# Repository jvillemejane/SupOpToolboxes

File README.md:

# SupOpToolboxes

**Toolboxes of functions for physicists in photonics**

*Developed by Institut d'Optiqe Graduate School / France*

This project is still **in development**. To contribute, look at the *Collaboration* section.

## Table of Contents
0. [About SupOptique](#about-supoptique)
1. [General Info](#general-info)
2. [Installation](#installation)
3. [How To Use](#how-to-use)
4. [Collaboration](#collaboration)
5. [FAQs](#faqs)

## About SupOptique
Founded in 1917, the Institut d'Optique Graduate School is a world leader in higher education, research and innovation in optics and photonics.

The Institut trains physics engineers, master's students and some of the most innovative PhDs in business and academia.
At the heart of networks of excellence, its international influence is based both on the quality of the training it provides and on its research and technology transfer.

The Institut is a major engineering school member of University Paris-Saclay and is established on the campuses of excellence of Paris-Saclay and Bordeaux, as well as Saint-Etienne.

The scientific contributions of its research center are major : the researchers publish on average one article per week and are quoted 30 times daily.

For more informations : [Institut d'Optique](https://www.institutoptique.fr/en)

## General Info

This repository contains :

- **Python Libraries** for physicists (*python_lib* directory)
- **Python Examples** for physicists (*python_examples* directory)
- **Embedded Librairies** for embedded systems development (Arduino, STM32 MBED, STM32 HAL...)
- **Engineers and Physicits Courses and Problems** (engineers training)

## Installation

You can **clone** this repository into your own work directory (using git) :

```
git clone https://github.com/jvillemejane/SupOpToolboxes.git
```

or

```
git clone git@github.com:jvillemejane/SupOpToolboxes.git
```

If you're not familiar to Git repository, you can also **download** the [archived file - zip](https://github.com/jvillemejane/SupOpToolboxes/archive/refs/heads/main.zip) of the repository.

## How To Use

### Python Libraries

To use **Python Libraries**, you can add the *python_lib* directory to the PYTHONPATH of your Python development interface. 

For example, in **Spyder**, you can select `TOOLS > PYTHONPATH` and add the path to *python_lib* directory.

### Python Examples

## Collaboration

## FAQs

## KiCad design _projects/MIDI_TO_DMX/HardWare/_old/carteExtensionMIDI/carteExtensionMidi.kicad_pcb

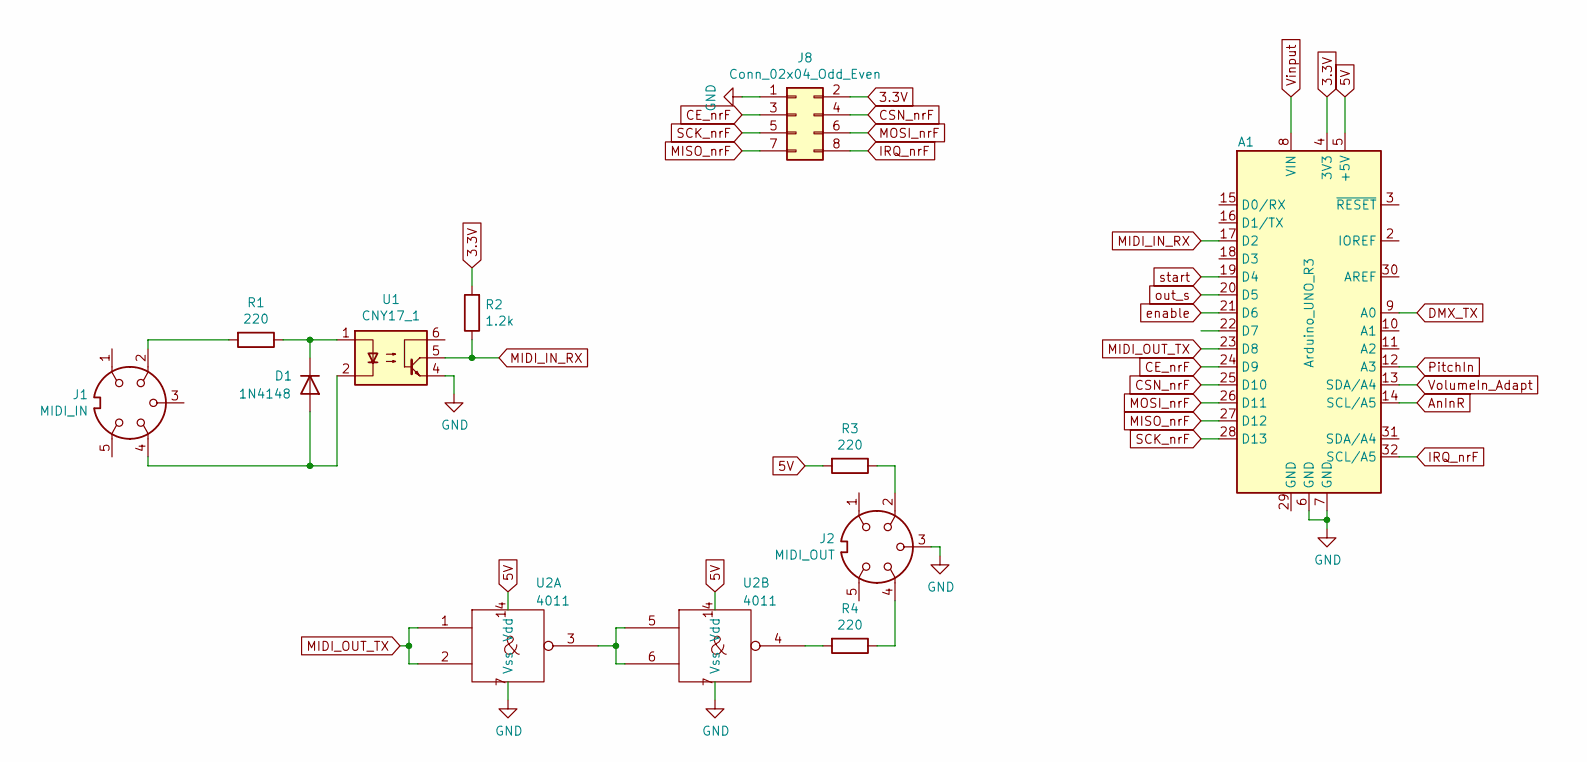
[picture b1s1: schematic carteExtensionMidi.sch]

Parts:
A1: Arduino_UNO_R3
D1: 1N4148; D_DO-35_SOD27_P7.62mm_Horizontal
J1: MIDI_IN; PinHeader_1x05_P2.54mm_Vertical
J2: MIDI_OUT; PinHeader_1x05_P2.54mm_Vertical
J8: Conn_02x04_Odd_Even; PinHeader_2x04_P2.54mm_Vertical
R1, R3, R4: 220; R_Axial_DIN0207_L6.3mm_D2.5mm_P10.16mm_Horizontal
R2: 1.2k; R_Axial_DIN0207_L6.3mm_D2.5mm_P10.16mm_Horizontal
U1: CNY17_1; DIP-6_W7.62mm_LongPads
U2: 4011; DIP-14_W7.62mm_LongPads

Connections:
3.3V: A1.4 (3V3), J8.2, R2.2
5V: A1.5 (+5V), R3.2, U2.14 (Vdd)
AnInR: A1.14 (SCL/A5)
CE_nrF: A1.24 (D9), J8.3
CSN_nrF: A1.25 (D10), J8.4
DMX_TX: A1.9 (A0)
GND: A1.6 (GND), A1.7 (GND), J2.3, J8.1, U1.4, U2.7 (Vss)
IRQ_nrF: A1.32 (SCL/A5), J8.8
MIDI_IN_RX: A1.17 (D2), R2.1, U1.5
MIDI_OUT_TX: A1.23 (D8), U2.1, U2.2
MISO_nrF: A1.27 (D12), J8.7
MOSI_nrF: A1.26 (D11), J8.6
unnamed: D1.1 (K), R1.1, U1.1
unnamed: D1.2 (A), J1.4, U1.2
unnamed: J1.2, R1.2
unnamed: J2.2, R3.1
unnamed: J2.4, R4.1
unnamed: R4.2, U2.4
unnamed: U2.3, U2.5, U2.6
PitchIn: A1.12 (A3)
SCK_nrF: A1.28 (D13), J8.5
Vinput: A1.8 (VIN)
VolumeIn_Adapt: A1.13 (SDA/A4)
enable: A1.21 (D6)
out_s: A1.20 (D5)
start: A1.19 (D4)

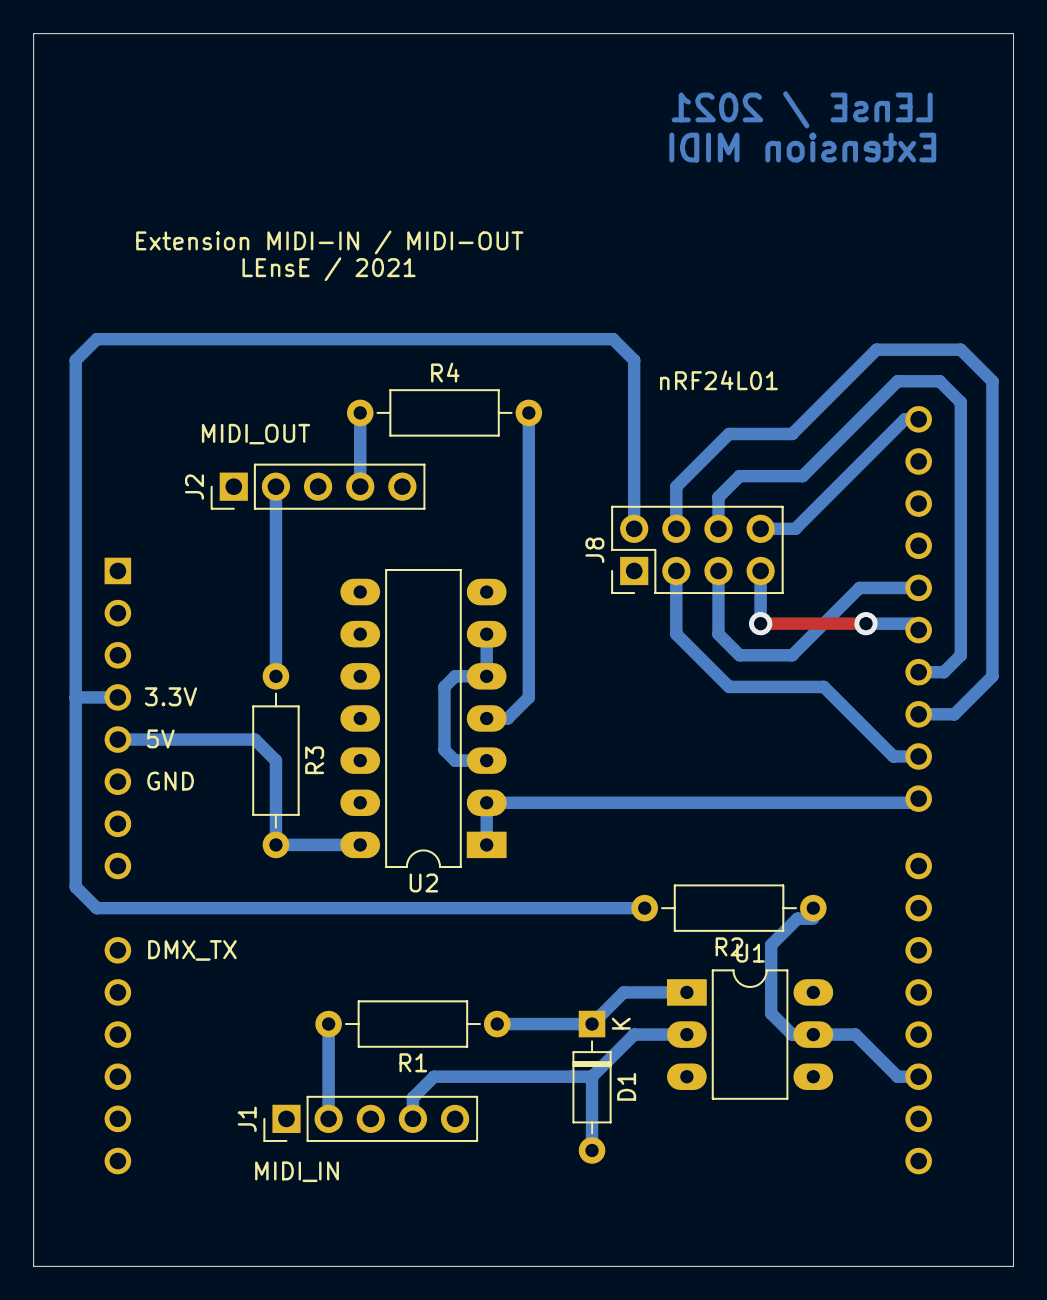
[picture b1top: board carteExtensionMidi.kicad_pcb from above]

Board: 2 copper layers, 59.1 x 74.3 mm, 11 parts (1 on the bottom side), 18 nets.

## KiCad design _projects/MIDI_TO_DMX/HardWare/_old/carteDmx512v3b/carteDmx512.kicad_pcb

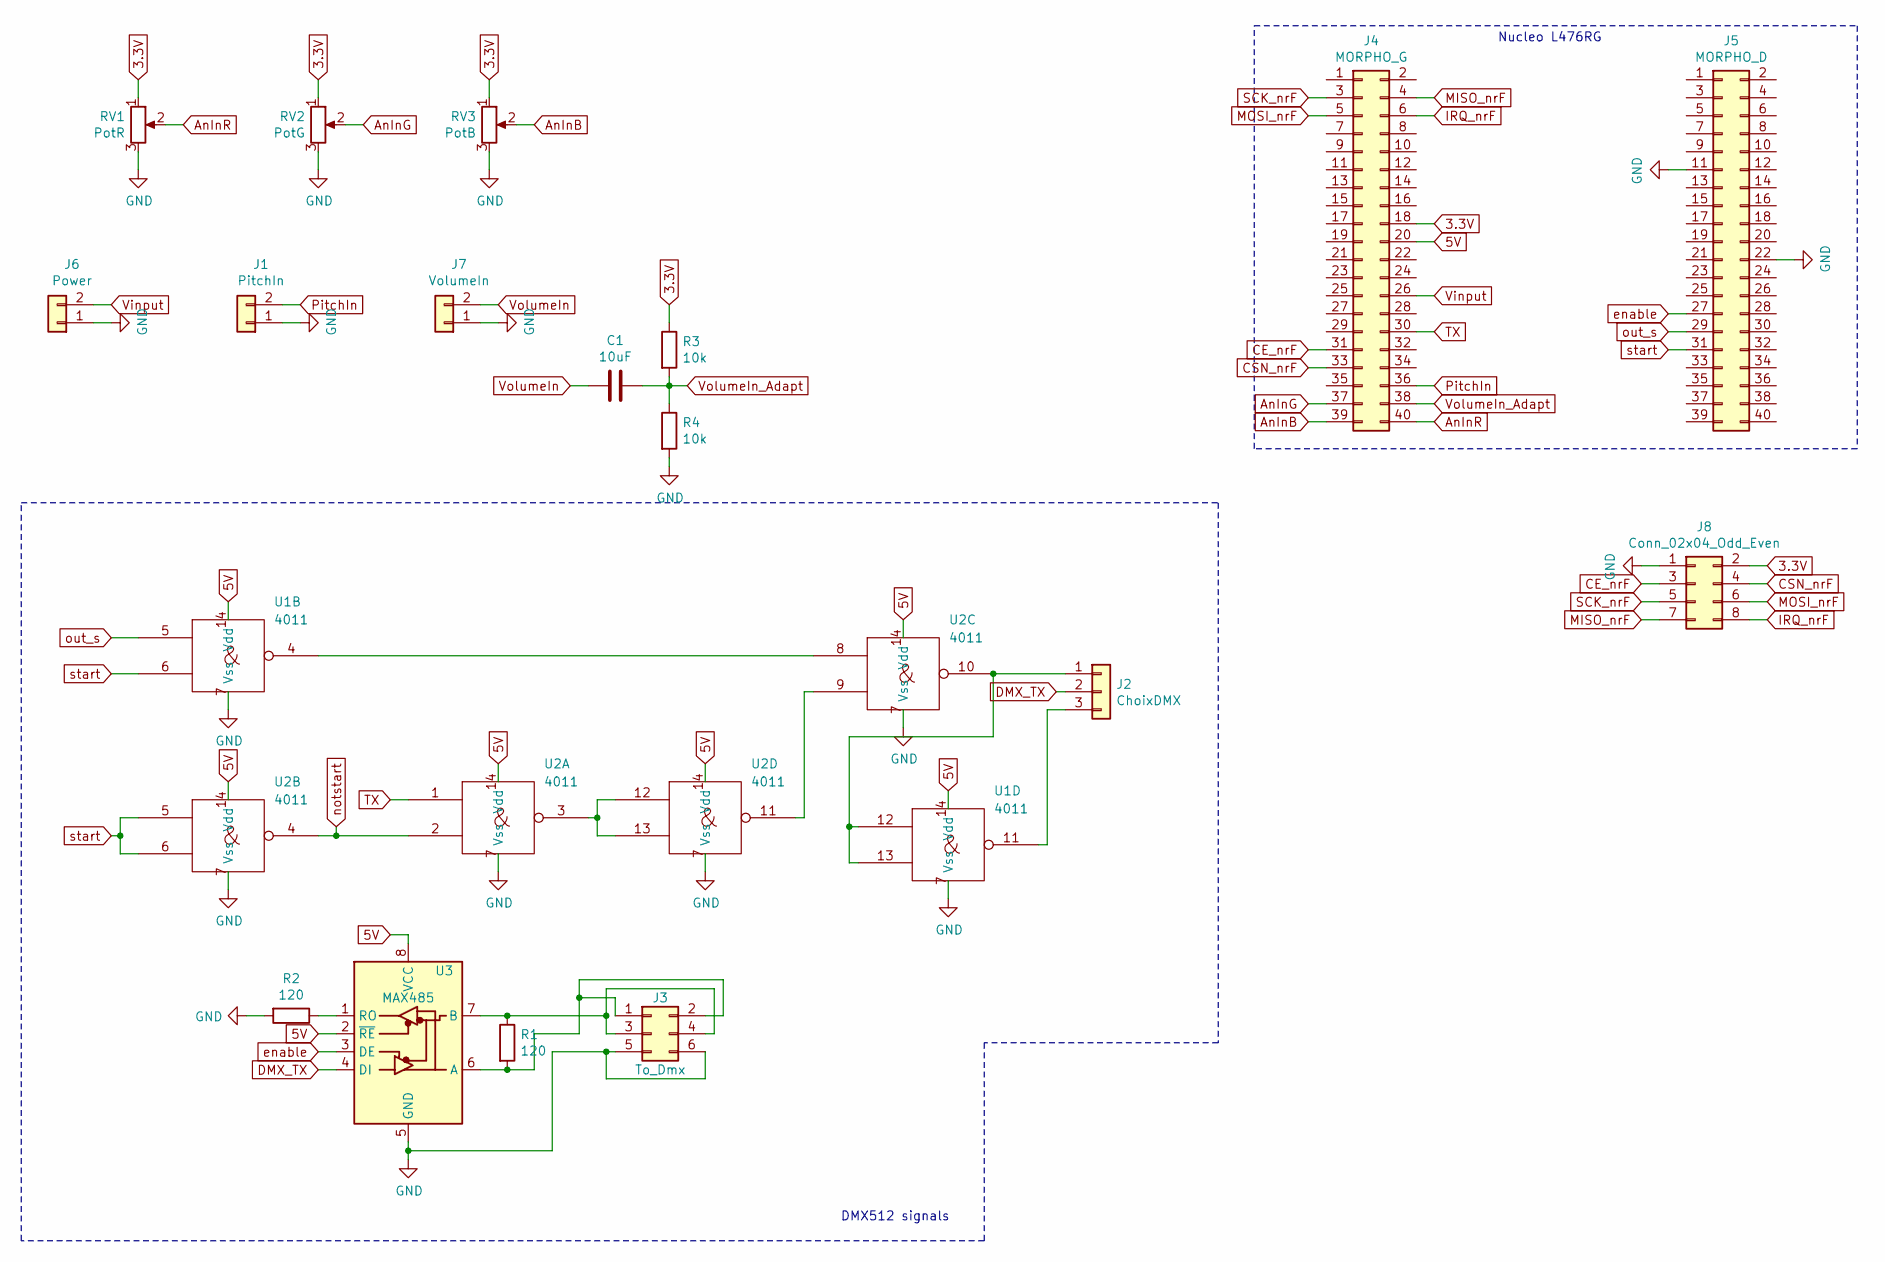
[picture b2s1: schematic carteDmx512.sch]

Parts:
C1: 10uF; CP_Radial_D5.0mm_P2.50mm
J1: PitchIn; TerminalBlock_Phoenix_MKDS-3-2-5.08_1x02_P5.08mm_Horizontal
J2: ChoixDMX; PinHeader_1x03_P2.54mm_Horizontal
J3: To_Dmx; PinHeader_2x03_P2.54mm_Vertical
J4: MORPHO_G; PinHeader_2x20_P2.54mm_Vertical
J5: MORPHO_D; PinHeader_2x20_P2.54mm_Vertical
J6: Power; TerminalBlock_Phoenix_MKDS-3-2-5.08_1x02_P5.08mm_Horizontal
J7: VolumeIn; TerminalBlock_Phoenix_MKDS-3-2-5.08_1x02_P5.08mm_Horizontal
J8: Conn_02x04_Odd_Even; PinHeader_2x04_P2.54mm_Vertical
R1, R2: 120; R_Axial_DIN0207_L6.3mm_D2.5mm_P10.16mm_Horizontal
R3, R4: 10k; R_Axial_DIN0207_L6.3mm_D2.5mm_P10.16mm_Horizontal
RV1: PotR; Potentiometer_Vishay_T73YP_Vertical
RV2: PotG; Potentiometer_Vishay_T73YP_Vertical
RV3: PotB; Potentiometer_Vishay_T73YP_Vertical
U1, U2: 4011; DIP-14_W7.62mm_Socket_LongPads
U3: MAX485; DIP-8_W7.62mm_Socket_LongPads

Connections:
3.3V: J4.18, J8.2, R3.1, RV1.1, RV2.1, RV3.1
5V: J4.20, U1.14 (Vdd), U2.14 (Vdd), U3.2 (~RE), U3.8 (VCC)
AnInB: J4.39, RV3.2
AnInG: J4.37, RV2.2
AnInR: J4.40, RV1.2
CE_nrF: J4.31, J8.3
CSN_nrF: J4.33, J8.4
DMX_TX: J2.2, U3.4 (DI)
GND: J1.1, J3.5, J3.6, J5.11, J5.22, J6.1, J7.1, J8.1, R2.2, R4.2, RV1.3, RV2.3, RV3.3, U1.7 (Vss), U2.7 (Vss), U3.5 (GND)
IRQ_nrF: J4.6, J8.8
MISO_nrF: J4.4, J8.7
MOSI_nrF: J4.5, J8.6
unnamed: J2.1, U1.12, U1.13, U2.10
unnamed: J2.3, U1.11
unnamed: J3.1, J3.2, R1.2, U3.6 (A)
unnamed: J3.3, J3.4, R1.1, U3.7 (B)
unnamed: R2.1, U3.1 (RO)
unnamed: U1.4, U2.8
unnamed: U2.9, U2.11
unnamed: U2.3, U2.12, U2.13
PitchIn: J1.2, J4.36
SCK_nrF: J4.3, J8.5
TX: J4.30, U2.1
Vinput: J4.26, J6.2
VolumeIn: C1.2, J7.2
VolumeIn_Adapt: C1.1, J4.38, R3.2, R4.1
enable: J5.27, U3.3 (DE)
notstart: U2.2, U2.4
out_s: J5.29, U1.5
start: J5.31, U1.6, U2.5, U2.6

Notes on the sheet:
Nucleo L476RG
DMX512 signals

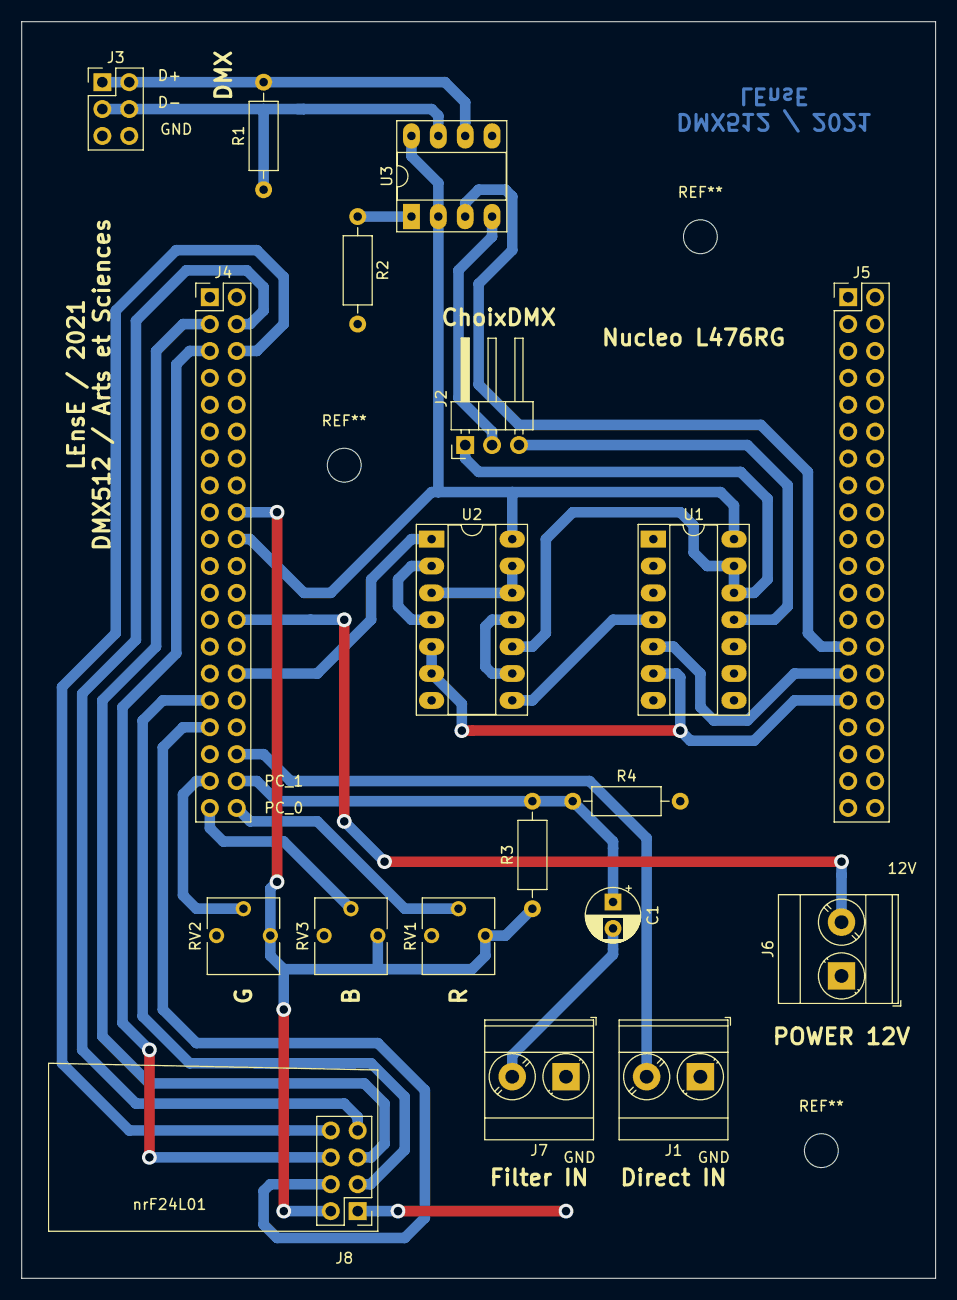
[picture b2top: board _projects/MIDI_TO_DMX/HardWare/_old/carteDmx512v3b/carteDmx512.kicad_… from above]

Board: 2 copper layers, 86.4 x 118.7 mm, 19 parts (0 on the bottom side), 30 nets.

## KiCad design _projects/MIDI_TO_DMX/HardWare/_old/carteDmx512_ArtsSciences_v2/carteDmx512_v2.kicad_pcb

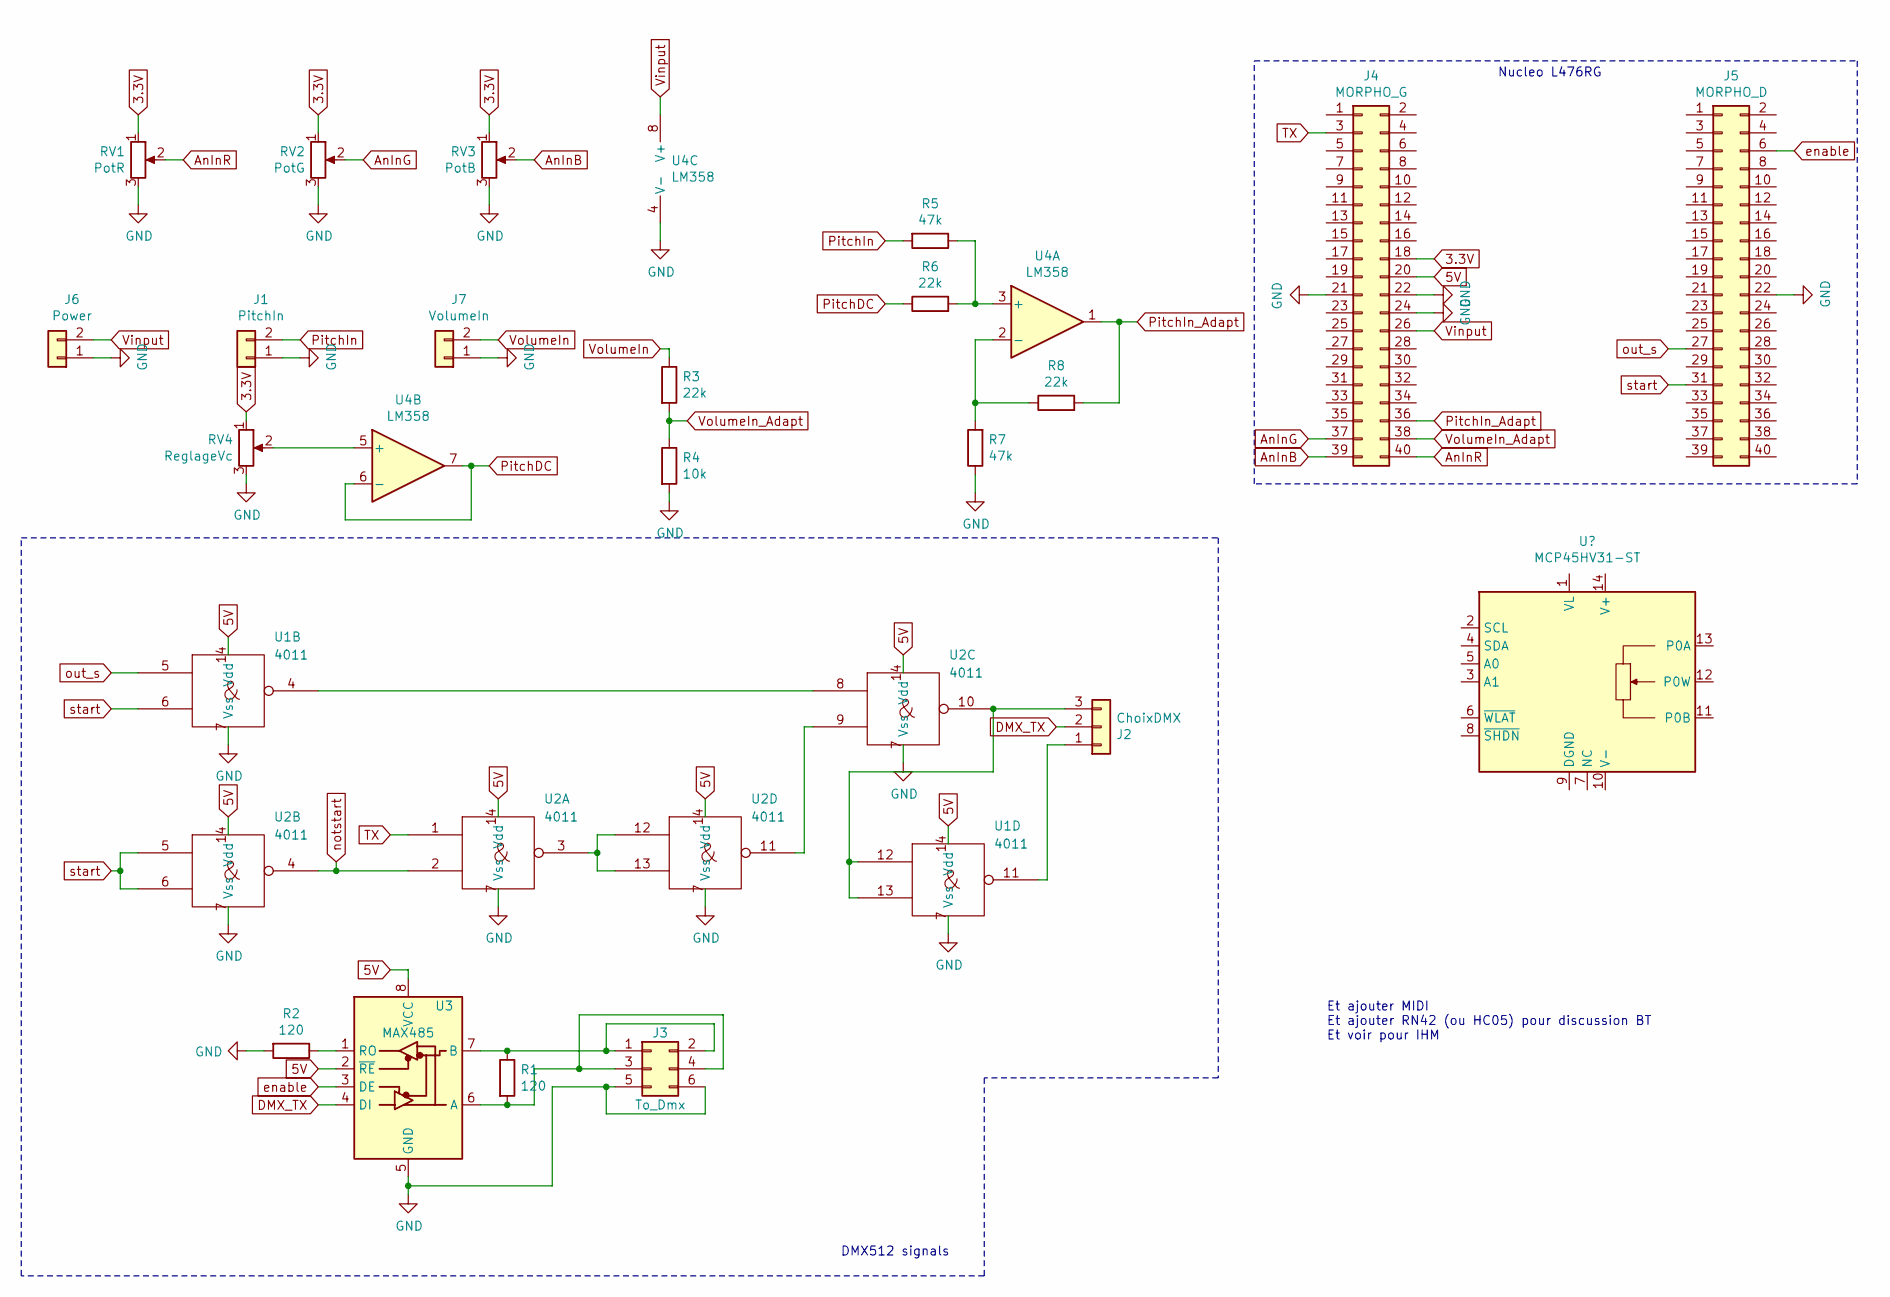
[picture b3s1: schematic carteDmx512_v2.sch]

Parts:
J1: PitchIn; TerminalBlock_Phoenix_MKDS-3-2-5.08_1x02_P5.08mm_Horizontal
J2: ChoixDMX; PinHeader_1x03_P2.54mm_Horizontal
J3: To_Dmx; PinHeader_2x03_P2.54mm_Vertical
J4: MORPHO_G; PinHeader_2x20_P2.54mm_Vertical
J5: MORPHO_D; PinHeader_2x20_P2.54mm_Vertical
J6: Power; TerminalBlock_Phoenix_MKDS-3-2-5.08_1x02_P5.08mm_Horizontal
J7: VolumeIn; TerminalBlock_Phoenix_MKDS-3-2-5.08_1x02_P5.08mm_Horizontal
R1, R2: 120; R_Axial_DIN0207_L6.3mm_D2.5mm_P10.16mm_Horizontal
R3, R6, R8: 22k; R_Axial_DIN0207_L6.3mm_D2.5mm_P10.16mm_Horizontal
R4: 10k; R_Axial_DIN0207_L6.3mm_D2.5mm_P10.16mm_Horizontal
R5, R7: 47k; R_Axial_DIN0207_L6.3mm_D2.5mm_P10.16mm_Horizontal
RV1: PotR; Potentiometer_Vishay_T73YP_Vertical
RV2: PotG; Potentiometer_Vishay_T73YP_Vertical
RV3: PotB; Potentiometer_Vishay_T73YP_Vertical
RV4: ReglageVc; Potentiometer_Vishay_T73YP_Vertical
U1, U2: 4011; DIP-14_W7.62mm_Socket_LongPads
U3: MAX485; DIP-8_W7.62mm_Socket_LongPads
U4: LM358; DIP-8_W7.62mm_Socket_LongPads

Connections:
3.3V: J4.18, RV1.1, RV2.1, RV3.1, RV4.1
5V: J4.20, U1.14 (Vdd), U2.14 (Vdd), U3.2 (~RE), U3.8 (VCC)
AnInB: J4.39, RV3.2
AnInG: J4.37, RV2.2
AnInR: J4.40, RV1.2
DMX_TX: J2.2, U3.4 (DI)
GND: J1.1, J3.5, J3.6, J4.21, J4.22, J4.24, J5.22, J6.1, J7.1, R2.2, R4.2, R7.1, RV1.3, RV2.3, RV3.3, RV4.3, U1.7 (Vss), U2.7 (Vss), U3.5 (GND), U4.4 (V-)
unnamed: J2.1, U1.11
unnamed: J2.3, U1.12, U1.13, U2.10
unnamed: J3.1, J3.2, R1.1, U3.7 (B)
unnamed: J3.3, J3.4, R1.2, U3.6 (A)
unnamed: R2.1, U3.1 (RO)
unnamed: R5.1, R6.2, U4.3 (+)
unnamed: R7.2, R8.1, U4.2 (-)
unnamed: RV4.2, U4.5 (+)
unnamed: U1.4, U2.8
unnamed: U2.9, U2.11
unnamed: U2.3, U2.12, U2.13
PitchDC: R6.1, U4.6 (-), U4.7
PitchIn: J1.2, R5.2
PitchIn_Adapt: J4.36, R8.2, U4.1
TX: J4.3, U2.1
Vinput: J4.26, J6.2, U4.8 (V+)
VolumeIn: J7.2, R3.1
VolumeIn_Adapt: J4.38, R3.2, R4.1
enable: J5.6, U3.3 (DE)
notstart: U2.2, U2.4
out_s: J5.27, U1.5
start: J5.31, U1.6, U2.5, U2.6

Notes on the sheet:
Nucleo L476RG
DMX512 signals
Et ajouter MIDI Et ajouter RN42 (ou HC05) pour discussion BT Et voir pour IHM

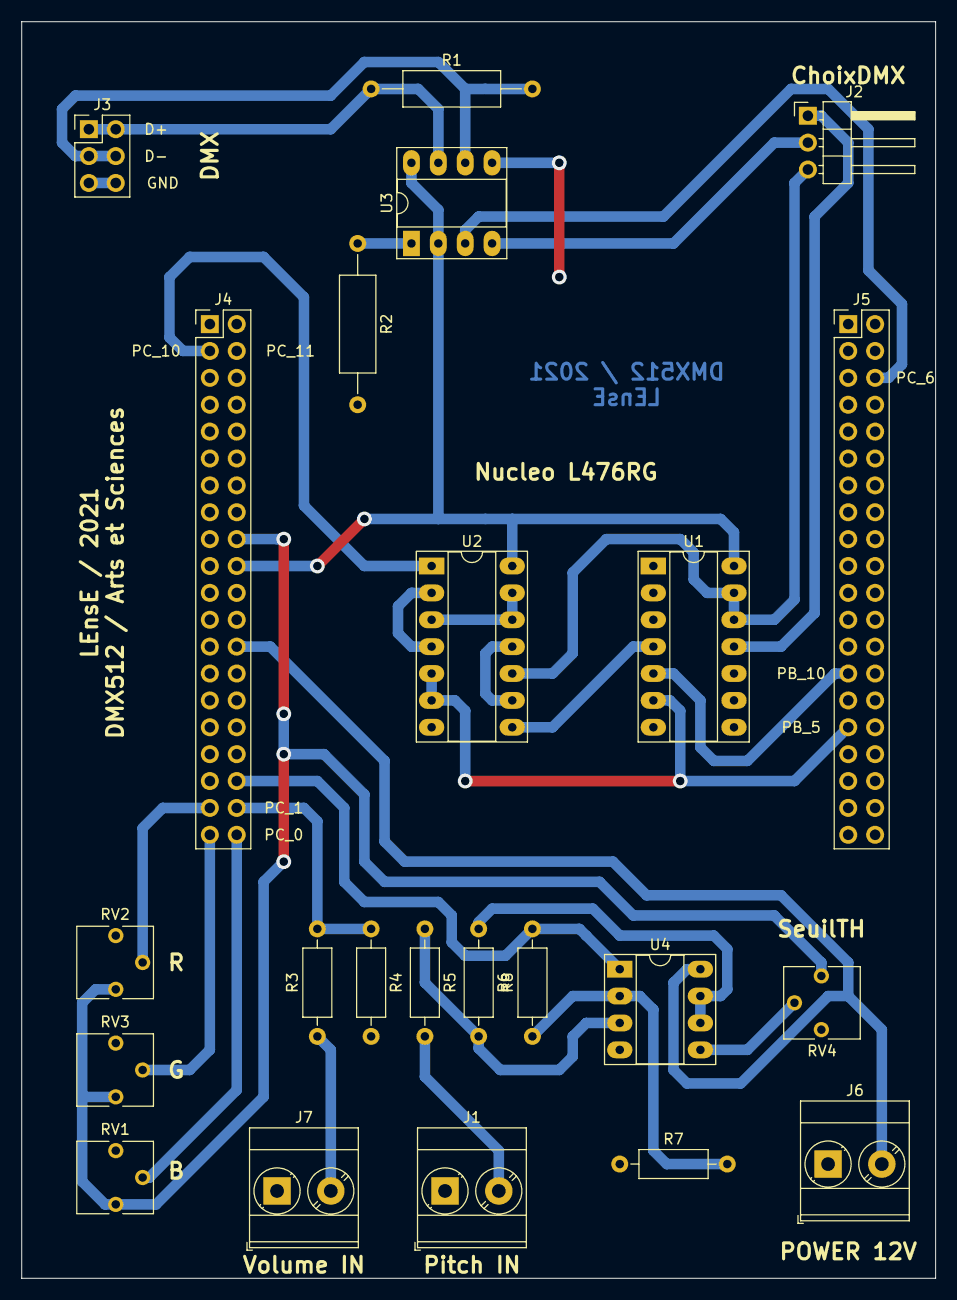
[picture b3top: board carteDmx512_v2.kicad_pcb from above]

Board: 2 copper layers, 86.4 x 118.7 mm, 23 parts (0 on the bottom side), 29 nets.

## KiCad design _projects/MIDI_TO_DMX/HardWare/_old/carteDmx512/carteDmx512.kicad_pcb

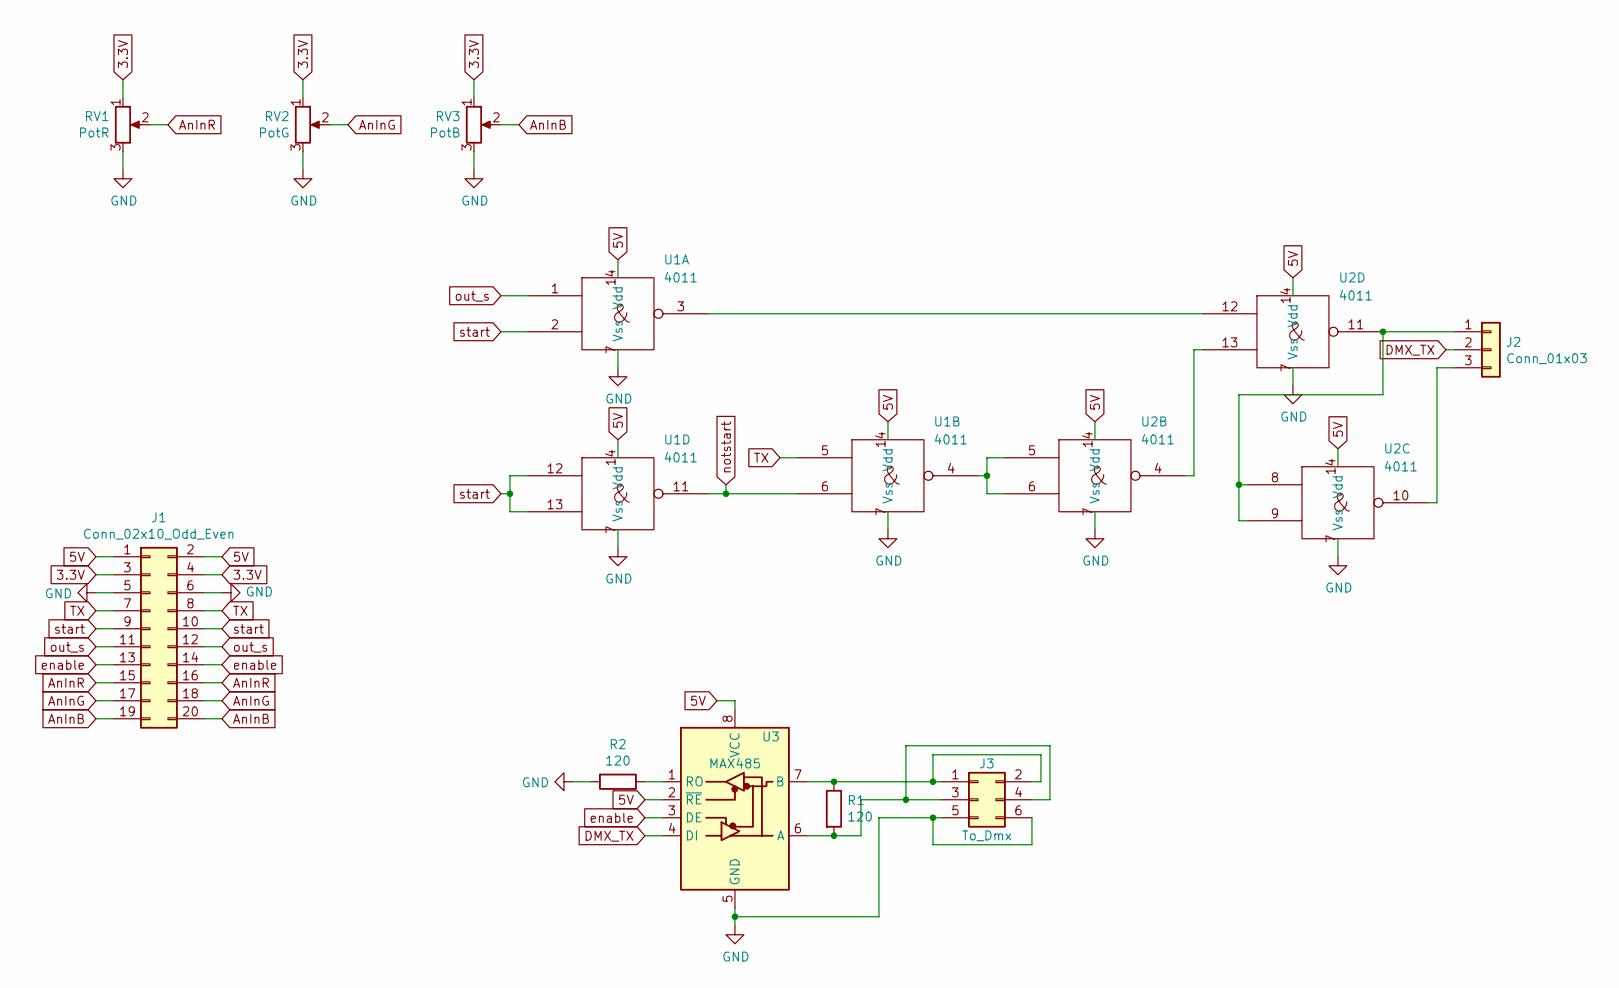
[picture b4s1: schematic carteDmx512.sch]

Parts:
J1: Conn_02x10_Odd_Even; PinHeader_2x10_P2.54mm_Vertical
J2: Conn_01x03; PinHeader_1x03_P2.54mm_Vertical
J3: To_Dmx; PinHeader_2x03_P2.54mm_Vertical
R1, R2: 120; R_Axial_DIN0309_L9.0mm_D3.2mm_P15.24mm_Horizontal
RV1: PotR; Potentiometer_Vishay_T73YP_Vertical
RV2: PotG; Potentiometer_Vishay_T73YP_Vertical
RV3: PotB; Potentiometer_Vishay_T73YP_Vertical
U1, U2: 4011; DIP-14_W7.62mm_Socket_LongPads
U3: MAX485; DIP-8_W7.62mm_Socket_LongPads

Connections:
3.3V: J1.3, J1.4, RV1.1, RV2.1, RV3.1
5V: J1.1, J1.2, U1.14 (Vdd), U2.14 (Vdd), U3.2 (~RE), U3.8 (VCC)
AnInB: J1.19, J1.20, RV3.2
AnInG: J1.17, J1.18, RV2.2
AnInR: J1.15, J1.16, RV1.2
DMX_TX: J2.2, U3.4 (DI)
GND: J1.5, J1.6, J3.5, J3.6, R2.2, RV1.3, RV2.3, RV3.3, U1.7 (Vss), U2.7 (Vss), U3.5 (GND)
unnamed: J2.1, U2.8, U2.9, U2.11
unnamed: J2.3, U2.10
unnamed: J3.1, J3.2, R1.1, U3.7 (B)
unnamed: J3.3, J3.4, R1.2, U3.6 (A)
unnamed: R2.1, U3.1 (RO)
unnamed: U1.3, U2.12
unnamed: U1.4, U2.5, U2.6
unnamed: U2.4, U2.13
TX: J1.7, J1.8, U1.5
enable: J1.13, J1.14, U3.3 (DE)
notstart: U1.6, U1.11
out_s: J1.11, J1.12, U1.1
start: J1.9, J1.10, U1.2, U1.12, U1.13

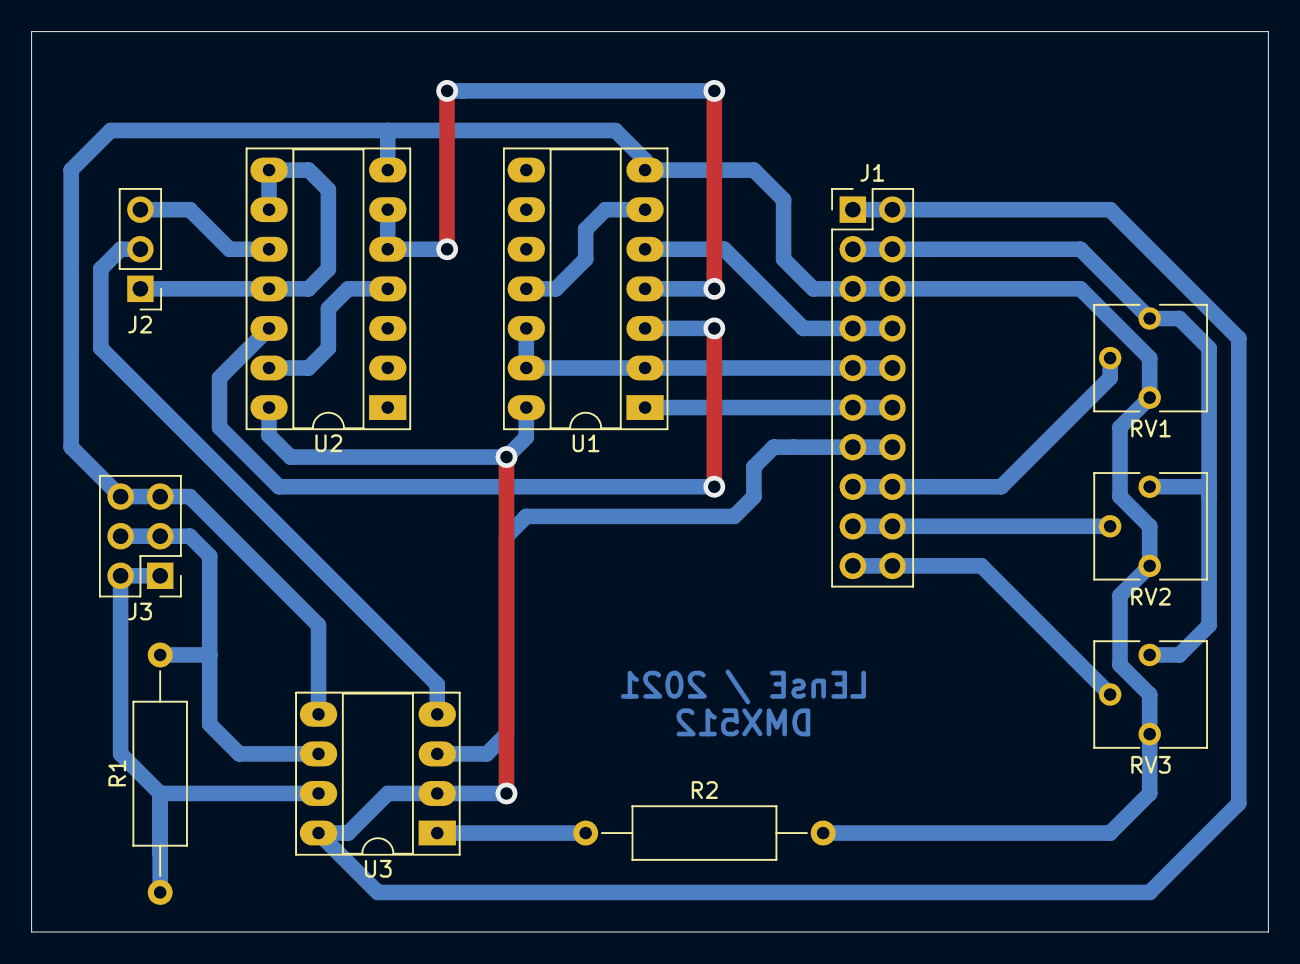
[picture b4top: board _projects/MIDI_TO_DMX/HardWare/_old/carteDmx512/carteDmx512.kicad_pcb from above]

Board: 2 copper layers, 79.4 x 57.8 mm, 11 parts (0 on the bottom side), 20 nets.

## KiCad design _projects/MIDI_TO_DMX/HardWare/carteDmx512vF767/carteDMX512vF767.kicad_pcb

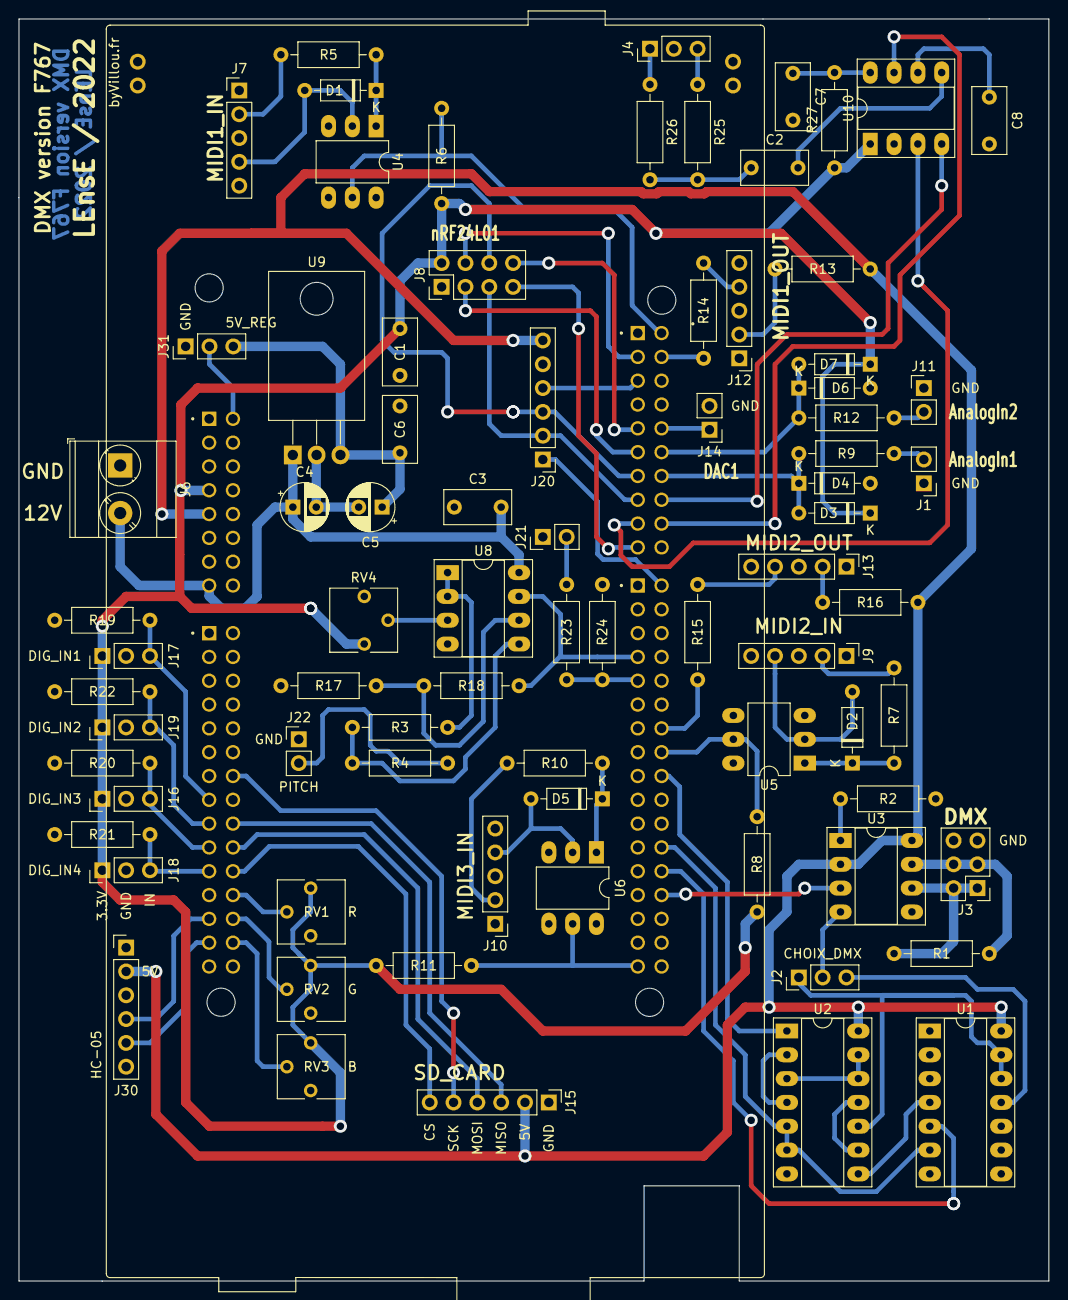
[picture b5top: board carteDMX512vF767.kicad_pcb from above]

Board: 2 copper layers, 109.9 x 134.6 mm, 79 parts (0 on the bottom side), 81 nets.

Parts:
C1, C3, C6, C8: 100nF; C_Rect_L7.0mm_W3.5mm_P5.00mm
C2: 10nF; C_Rect_L7.0mm_W3.5mm_P5.00mm
C4, C5: 100uF; CP_Radial_D5.0mm_P2.50mm
C7: 33pF; C_Rect_L7.0mm_W3.5mm_P5.00mm
D1, D2, D3, D4, D5, D6, D7: 1N4148; D_DO-35_SOD27_P7.62mm_Horizontal
J1: DirectIn; PinHeader_1x02_P2.54mm_Vertical
J2: ChoixDMX; PinHeader_1x03_P2.54mm_Vertical
J3: To_Dmx; PinHeader_2x03_P2.54mm_Vertical
J4: JackInStereo; PinHeader_1x03_P2.54mm_Vertical
J6: Power; TerminalBlock_Phoenix_MKDS-3-2-5.08_1x02_P5.08mm_Horizontal
J7: MIDI1_IN; PinHeader_1x05_P2.54mm_Vertical
J8: nRF24L01; PinHeader_2x04_P2.54mm_Vertical
J9: MIDI2_IN; PinHeader_1x05_P2.54mm_Vertical
J10: MIDI3_IN; PinHeader_1x05_P2.54mm_Vertical
J11: FilterIn; PinHeader_1x02_P2.54mm_Vertical
J12: MIDI1_OUT; PinHeader_1x05_P2.54mm_Vertical
J13: MIDI2_OUT; PinHeader_1x05_P2.54mm_Vertical
J14: Test_D13; PinHeader_1x02_P2.54mm_Vertical
J15: SD_Card; PinHeader_1x06_P2.54mm_Vertical
J16: DigIn3; PinHeader_1x03_P2.54mm_Vertical
J17: DigIn1; PinHeader_1x03_P2.54mm_Vertical
J18: DigIn4; PinHeader_1x03_P2.54mm_Vertical
J19: DigIn2; PinHeader_1x03_P2.54mm_Vertical
J20: LCD_Out; PinHeader_1x06_P2.54mm_Vertical
J21: Volume_In_In; PinHeader_1x02_P2.54mm_Vertical
J22: Pitch_In_In; PinHeader_1x02_P2.54mm_Vertical
J30: BT_HC05; PinHeader_1x06_P2.54mm_Vertical
J31: BandeauLED; PinHeader_1x03_P2.54mm_Vertical
R1, R2: 120; R_Axial_DIN0207_L6.3mm_D2.5mm_P10.16mm_Horizontal
R3, R18, R23, R25, R26: 22k; R_Axial_DIN0207_L6.3mm_D2.5mm_P10.16mm_Horizontal
R4, R17: 47k; R_Axial_DIN0207_L6.3mm_D2.5mm_P10.16mm_Horizontal
R5, R7, R10, R13, R14, R15, R16: 220; R_Axial_DIN0207_L6.3mm_D2.5mm_P10.16mm_Horizontal
R6, R8, R9, R11, R12: 1.2k; R_Axial_DIN0207_L6.3mm_D2.5mm_P10.16mm_Horizontal
R19, R20, R21, R22, R24: 10k; R_Axial_DIN0207_L6.3mm_D2.5mm_P10.16mm_Horizontal
R27: 220k; R_Axial_DIN0207_L6.3mm_D2.5mm_P10.16mm_Horizontal
RV1: PotR; Potentiometer_Vishay_T73YP_Vertical
RV2: PotG; Potentiometer_Vishay_T73YP_Vertical
RV3: PotB; Potentiometer_Vishay_T73YP_Vertical
RV4: 22k; Potentiometer_Vishay_T73YP_Vertical
U1, U2: 4011; DIP-14_W7.62mm_Socket_LongPads
U3: MAX485; DIP-8_W7.62mm_Socket_LongPads
U4, U5, U6: CNY17-1; DIP-6_W7.62mm_LongPads
U7: NUCLEO144-H7A3ZI-Q; ST_Zio_Connectors_144_STLink
U8: LM358; DIP-8_W7.62mm_Socket_LongPads
U9: L7805; TO-220-3_Horizontal_TabDown
U10: MSGEQ7; DIP-8_W7.62mm_Socket_LongPads

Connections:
3.3V: C1.2, D3.1, D6.1, J8.2, J16.1, J17.1, J18.1, J19.1, R6.2, R8.2, R11.2, R27.1, RV1.1, RV2.1, RV3.1, RV4.1, U7.CN8_7, U10.1
5V: J15.2, J20.6, J30.2, R13.2, R16.2, U1.14, U2.14, U3.2, U3.8, U7.CN8_9
5V_REG: C5.1, C6.2, J31.3, U9.3
AnInB: RV3.2, U7.CN9_28
AnInG: RV2.2, U7.CN9_26
AnInR: RV1.2, U7.CN9_24
AnalogIn1: D3.2, D4.1, R9.2, U7.CN7_14
AnalogIn2: D6.2, D7.1, R12.2, U7.CN7_12
Bandeau_LED: J31.2, U7.CN8_2
CE_nrF: J8.3, U7.CN7_11
CSN_nrF: J8.4, U7.CN7_3
CS_LCD: J20.4, U7.CN7_5
CS_SDCar: J15.6, U7.CN9_22
DAC1: J14.1, U7.CN7_10
DIG_IN_1: J17.3, R19.1, U7.CN9_15
DIG_IN_2: J19.3, R22.1, U7.CN9_17
DIG_IN_3: J16.3, R20.1, U7.CN9_19
DIG_IN_4: J18.3, R21.1, U7.CN9_21
DMX_TX: J2.2, U3.4
EQ_Reset: U7.CN7_18, U10.7
EQ_Strobe: U7.CN7_16, U10.4
EQ_out: U7.CN7_17, U10.3
GND: C1.1, C3.1, C4.2, C5.2, C6.1, C7.2, C8.2, D4.2, D7.2, J1.1, J3.5, J3.6, J4.2, J6.1, J8.1, J11.1, J12.3, J13.3, J14.2, J15.1, J16.2, J17.2, J18.2, J19.2, J20.5, J21.1, J22.1, J30.3, J31.1, R2.2, R17.1, R19.2, R20.2, R21.2, R22.2, R24.2, RV1.3, RV2.3, RV3.3, RV4.3, U1.7, U2.7, U3.5, U4.4, U5.4, U6.4, U7.CN7_8, U7.CN8_11, U7.CN8_13, U7.CN9_12, U7.CN9_23, U8.4, U9.2, U10.2
IRQ_nrF: J8.8, U7.CN7_9
MIDI1_IN_RX: R6.1, U4.5, U7.CN7_2
MIDI1_OUT_TX: R14.2, U7.CN7_4
MIDI2_IN_RX: R8.1, U5.5, U7.CN10_16
MIDI2_OUT_TX: R15.2, U7.CN10_14
MIDI3_IN_RX: R11.1, U6.5, U7.CN10_33
MISO_SD: J15.3, U7.CN9_18
MISO_nrF: J8.7, U7.CN7_19
MOSI_SD: J15.4, U7.CN9_20
MOSI_nrF: J8.6, J20.3, U7.CN7_13
unnamed: C2.1, R25.2, R26.2
unnamed: C2.2, U10.5
unnamed: C7.1, R27.2, U10.8
unnamed: C8.1, U10.6
unnamed: D1.1, R5.1, U4.1
unnamed: D1.2, J7.4, U4.2
unnamed: D2.1, R7.1, U5.1
unnamed: D2.2, J9.4, U5.2
unnamed: D5.1, R10.1, U6.1
unnamed: D5.2, J10.4, U6.2
unnamed: J1.2, R9.1
unnamed: J2.1, U1.12, U1.13, U2.10
unnamed: J2.3, U1.11
unnamed: J3.1, J3.2, R1.2, U3.6
unnamed: J3.3, J3.4, R1.1, U3.7
unnamed: J4.1, R26.1
unnamed: J4.3, R25.1
unnamed: J7.2, R5.2
unnamed: J9.2, R7.2
unnamed: J10.2, R10.2
unnamed: J11.2, R12.1
unnamed: J12.2, R13.1
unnamed: J12.4, R14.1
unnamed: J13.2, R16.1
unnamed: J13.4, R15.1
unnamed: R2.1, U3.1
unnamed: R3.1, R4.1, U8.5
unnamed: R3.2, U8.1, U8.2
unnamed: R17.2, R18.2, U8.6
unnamed: RV4.2, U8.3
unnamed: U1.4, U2.8
unnamed: U2.9, U2.11
unnamed: U2.3, U2.12, U2.13
Pit_In: J22.2, R4.2
Pitch_In: R18.1, U7.CN10_7, U8.7
RS_LCD: J20.1, U7.CN10_2
RX_BT_HC05: J30.4, U7.CN9_25
SCK_SD: J15.5, U7.CN9_14
SCK_nrF: J8.5, J20.2, U7.CN7_15
TX_BT_HC05: J30.5, U7.CN9_27
TX_DMX: U2.1, U7.CN10_18
Vinput: C3.2, C4.1, J6.2, U7.CN8_15, U8.8, U9.1
Vol_In: J21.2, R23.1
Volume_In: R23.2, R24.1, U7.CN10_9
enable: U3.3, U7.CN10_28
notstart: U2.2, U2.4
out_s: U1.5, U7.CN10_26
start: U1.6, U2.5, U2.6, U7.CN10_24
